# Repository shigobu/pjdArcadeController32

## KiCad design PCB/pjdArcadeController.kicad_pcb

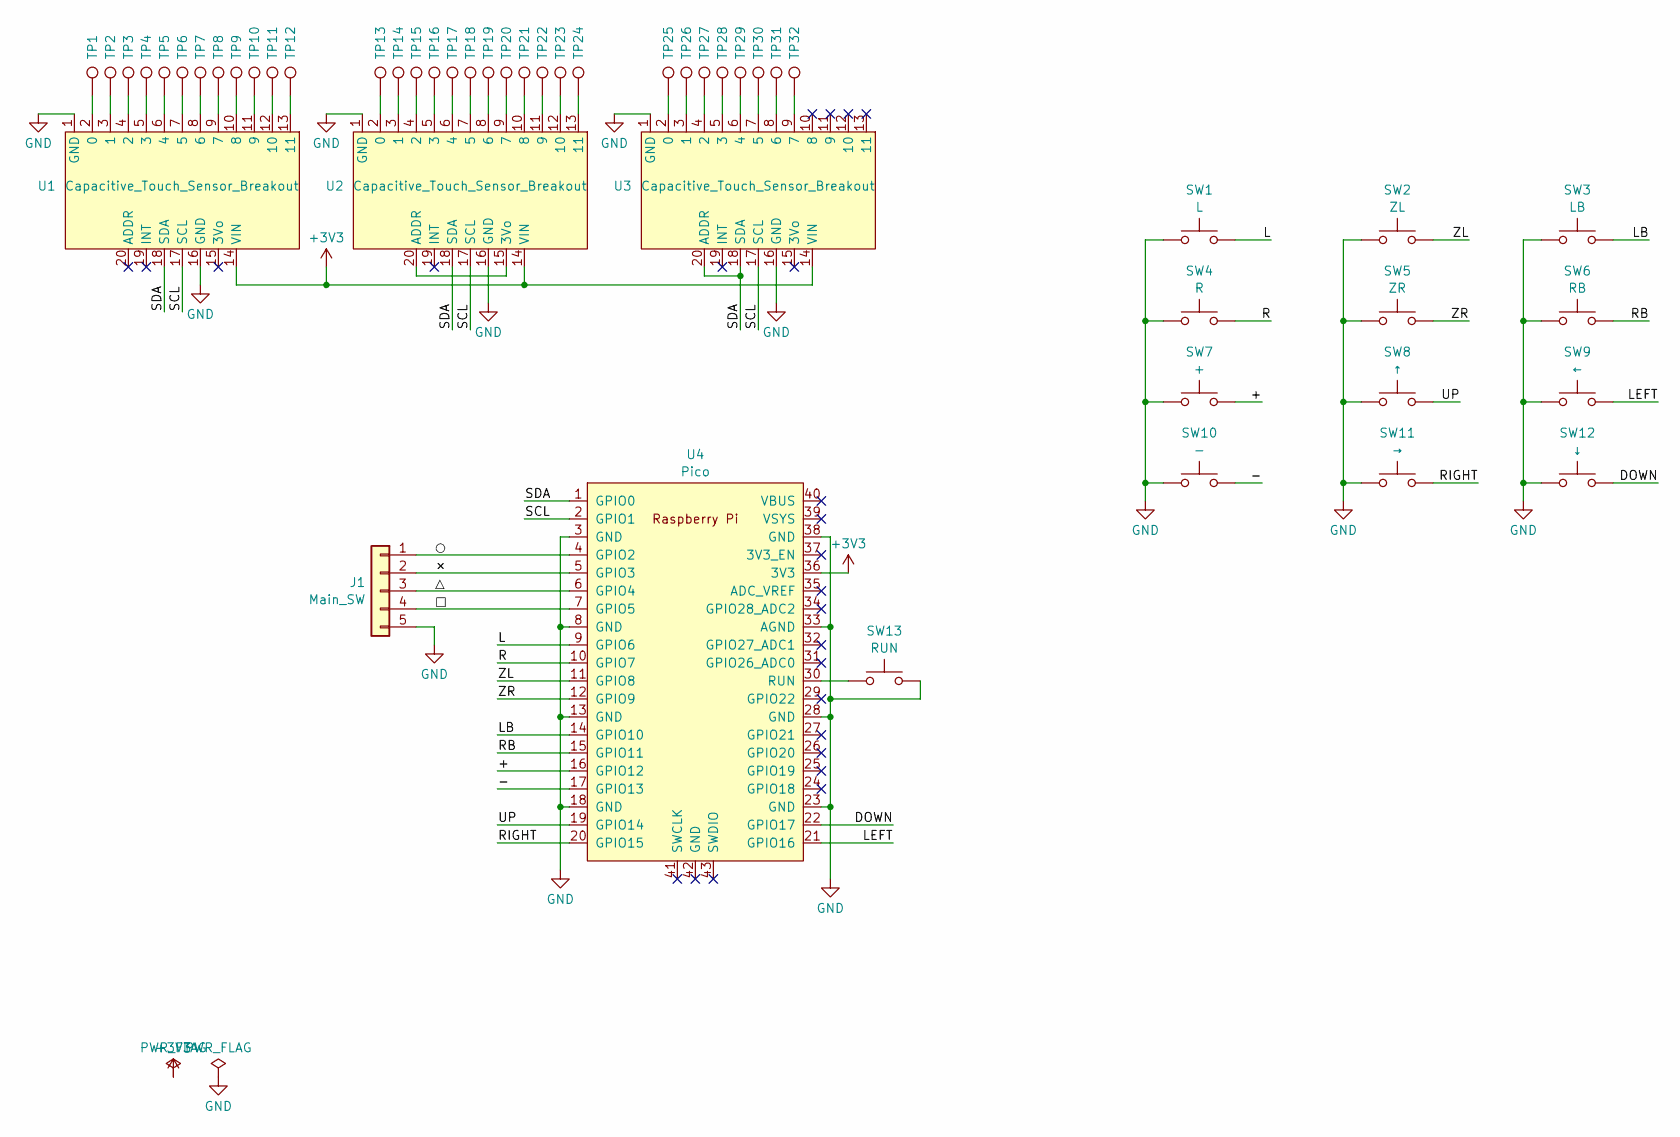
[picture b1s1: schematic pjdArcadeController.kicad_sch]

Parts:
J1: Main_SW; JST_XH_B5B-XH-A_1x05_P2.50mm_Vertical
SW1: L; SW_PUSH_6mm
SW2: ZL; SW_PUSH_6mm
SW3: LB; SW_PUSH_6mm
SW4: R; SW_PUSH_6mm
SW5: ZR; SW_PUSH_6mm
SW6: RB; SW_PUSH_6mm
SW7: +; SW_PUSH_6mm
SW8: ↑; SW_PUSH_6mm
SW9: ←; SW_PUSH_6mm
SW10: -; SW_PUSH_6mm
SW11: →; SW_PUSH_6mm
SW12: ↓; SW_PUSH_6mm
SW13: RUN; SW_PUSH_6mm
TP1, TP2, TP3, TP4, TP5, TP6, TP7, TP8, TP9, TP10, TP11, TP12, TP13, TP14, TP15, TP16, TP17, TP18, TP19, TP20, TP21, TP22, TP23, TP24, TP25, TP26, TP27, TP28, TP29, TP30, TP31, TP32: TestPoint; TouchBar
U1, U2, U3: Capacitive_Touch_Sensor_Breakout
U4: Pico; RPi_Pico_SMD_TH

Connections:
+3V3: U1.14 (VIN), U2.14 (VIN), U3.14 (VIN), U4.36 (3V3)
/+: SW7.2, U4.16 (GPIO12)
/-: SW10.2, U4.17 (GPIO13)
/DOWN: SW12.2, U4.22 (GPIO17)
/L: SW1.2, U4.9 (GPIO6)
/LB: SW3.2, U4.14 (GPIO10)
/LEFT: SW9.2, U4.21 (GPIO16)
/R: SW4.2, U4.10 (GPIO7)
/RB: SW6.2, U4.15 (GPIO11)
/RIGHT: SW11.2, U4.20 (GPIO15)
/SCL: U1.17 (SCL), U2.17 (SCL), U3.17 (SCL), U4.2 (GPIO1)
/SDA: U1.18 (SDA), U2.18 (SDA), U3.18 (SDA), U3.20 (ADDR), U4.1 (GPIO0)
/UP: SW8.2, U4.19 (GPIO14)
/ZL: SW2.2, U4.11 (GPIO8)
/ZR: SW5.2, U4.12 (GPIO9)
/×: J1.2, U4.5 (GPIO3)
/□: J1.4, U4.7 (GPIO5)
/△: J1.3, U4.6 (GPIO4)
/○: J1.1, U4.4 (GPIO2)
GND: J1.5, SW1.1, SW2.1, SW3.1, SW4.1, SW5.1, SW6.1, SW7.1, SW8.1, SW9.1, SW10.1, SW11.1, SW12.1, SW13.2, U1.1 (GND), U1.16 (GND), U2.1 (GND), U2.16 (GND), U3.1 (GND), U3.16 (GND), U4.3 (GND), U4.8 (GND), U4.13 (GND), U4.18 (GND), U4.23 (GND), U4.28 (GND), U4.33 (AGND), U4.38 (GND)
unnamed: TP1.1, U1.2 (0)
unnamed: TP2.1, U1.3 (1)
unnamed: TP3.1, U1.4 (2)
unnamed: TP4.1, U1.5 (3)
unnamed: TP5.1, U1.6 (4)
unnamed: TP6.1, U1.7 (5)
unnamed: TP7.1, U1.8 (6)
unnamed: TP8.1, U1.9 (7)
unnamed: TP9.1, U1.10 (8)
unnamed: TP10.1, U1.11 (9)
unnamed: TP11.1, U1.12 (10)
unnamed: TP12.1, U1.13 (11)
unnamed: TP13.1, U2.2 (0)
unnamed: TP14.1, U2.3 (1)
unnamed: TP15.1, U2.4 (2)
unnamed: TP16.1, U2.5 (3)
unnamed: U2.15 (3Vo), U2.20 (ADDR)
unnamed: TP17.1, U2.6 (4)
unnamed: TP18.1, U2.7 (5)
unnamed: TP19.1, U2.8 (6)
unnamed: TP20.1, U2.9 (7)
unnamed: TP21.1, U2.10 (8)
unnamed: TP22.1, U2.11 (9)
unnamed: TP23.1, U2.12 (10)
unnamed: TP24.1, U2.13 (11)
unnamed: TP25.1, U3.2 (0)
unnamed: TP26.1, U3.3 (1)
unnamed: TP27.1, U3.4 (2)
unnamed: TP28.1, U3.5 (3)
unnamed: TP29.1, U3.6 (4)
unnamed: TP30.1, U3.7 (5)
unnamed: TP31.1, U3.8 (6)
unnamed: TP32.1, U3.9 (7)
unnamed: SW13.1, U4.30 (RUN)

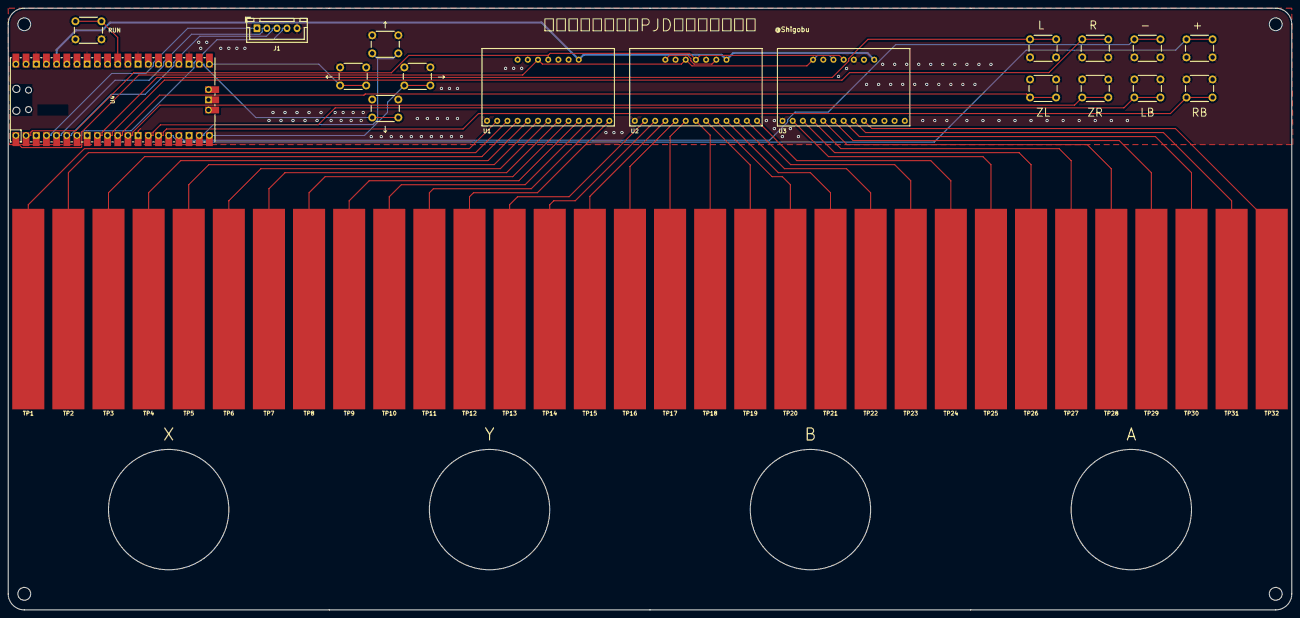
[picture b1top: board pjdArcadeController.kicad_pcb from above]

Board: 2 copper layers, 320.0 x 150.0 mm, 54 parts (0 on the bottom side), 54 nets.

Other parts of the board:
REF1, REF2, REF3, REF4: MountingHole_3.2mm_M3

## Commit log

2025-08-11 最初のコミット
2025-08-11 ソース・ファイル移動
2025-08-13 タッチセンサの値を読む
2025-08-13 タッチセンサの値をスティックに設定
2025-08-14 コンストラクタのautoconfigをtrueに設定
2025-08-15 ボタン番号修正。 コア間のデータ転送方法をfifoに変更。
2025-08-15 ボタン追加
2025-08-15 ボタン設定追加
